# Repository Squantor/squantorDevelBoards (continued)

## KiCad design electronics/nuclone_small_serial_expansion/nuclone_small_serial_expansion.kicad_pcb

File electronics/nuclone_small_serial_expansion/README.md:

# Nuclone expansion board with FTDI/UART connection
Nuclone expansion board with UART connection, prototyping area and some connections
# HSI (Hardware Software Interface)
No real HSI, UART RX/TX brought outside
## TODO's
Still some things need to be done:
* schematic entry 
* PCB layout
* Review with one night in between
* Produce at [OSHPARK](https://oshpark.com/)
* Assemble
* Test & characterise
* update Readme.md with pictures and BOM
## BOM
* bunch of JST-PH connectors

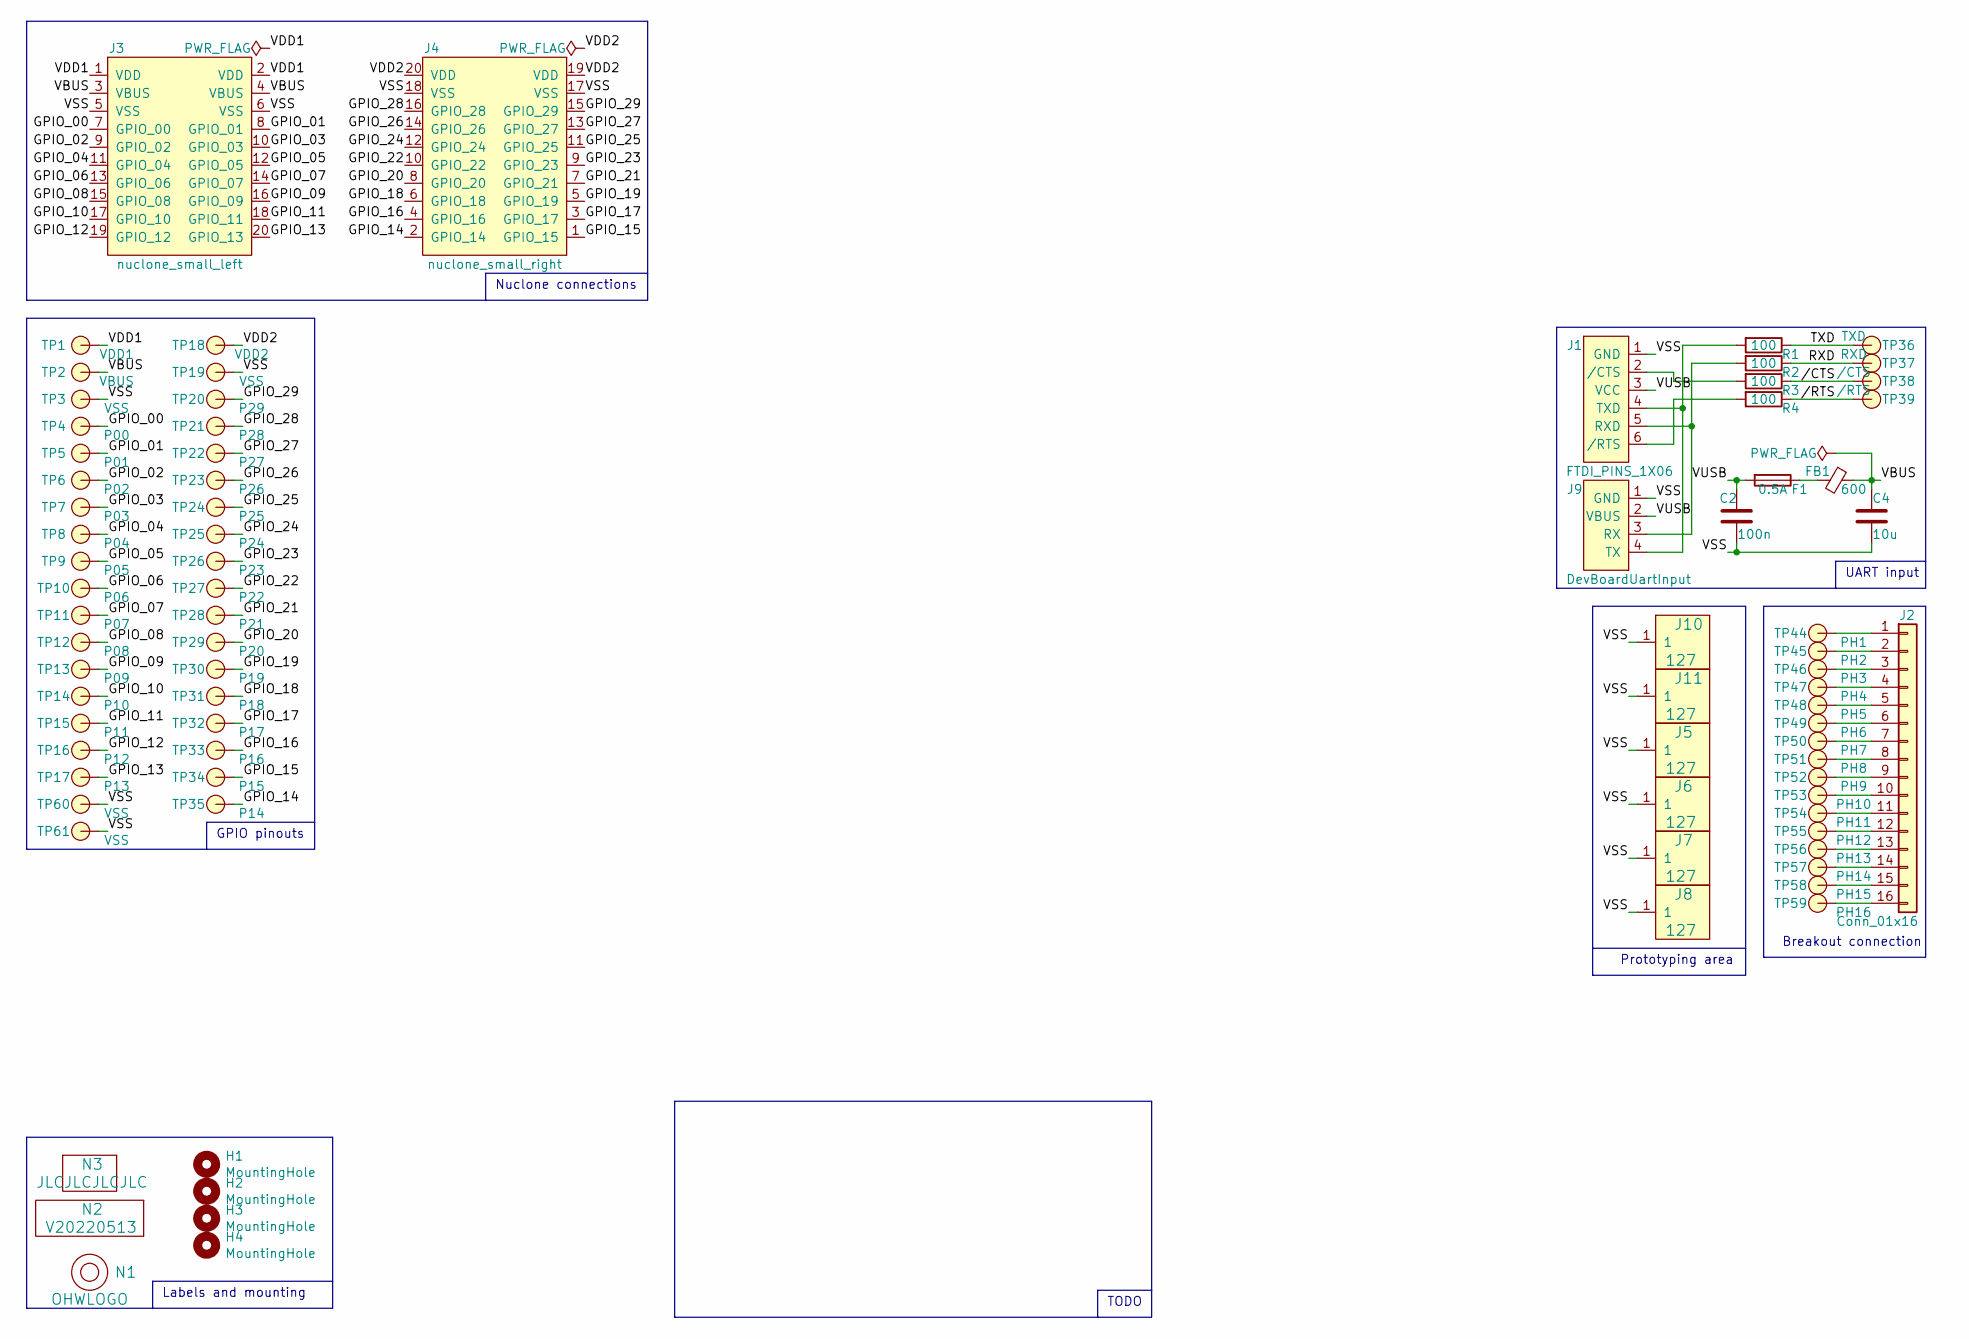
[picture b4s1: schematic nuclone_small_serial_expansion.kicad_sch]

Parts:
C2: 100n; C_0603
C4: 10u; C_0603
F1: 0.5A; F_0603_hand
FB1: 600; L_0603
H1, H2, H3, H4: MountingHole; MountingHole_3.2mm_M3_Pad_Via
J1: FTDI_PINS_1X06; PinHeader_1x06_P2.54mm_Horizontal
J2: Conn_01x16; JST_PH_S16B-PH-K_1x16_P2.00mm_Horizontal
J3: nuclone_small_left; nuclone_small_left_stacked
J4: nuclone_small_right; nuclone_small_right_stacked
J5, J6, J7, J8, J10, J11: 127; proto-SMD-0127-08X08-P010X020+pad
J9: DevBoardUartInput; JST_PH_S4B-PH-K_1x04_P2.00mm_Horizontal
N1: OHWLOGO; OSHW-Symbol_6.7x6mm_SilkScreen
N2: V20220513; Label_Generic
N3: JLCJLCJLCJLC; Label_Generic
R1, R2, R3, R4: 100; R_0603_hand
TP1: VDD1; TestPoint_hole_H05R10
TP2: VBUS; TestPoint_hole_H05R10
TP3, TP19, TP60, TP61: VSS; TestPoint_hole_H05R10
TP4: P00; TestPoint_hole_H05R10
TP5: P01; TestPoint_hole_H05R10
TP6: P02; TestPoint_hole_H05R10
TP7: P03; TestPoint_hole_H05R10
TP8: P04; TestPoint_hole_H05R10
TP9: P05; TestPoint_hole_H05R10
TP10: P06; TestPoint_hole_H05R10
TP11: P07; TestPoint_hole_H05R10
TP12: P08; TestPoint_hole_H05R10
TP13: P09; TestPoint_hole_H05R10
TP14: P10; TestPoint_hole_H05R10
TP15: P11; TestPoint_hole_H05R10
TP16: P12; TestPoint_hole_H05R10
TP17: P13; TestPoint_hole_H05R10
TP18: VDD2; TestPoint_hole_H05R10
TP20: P29; TestPoint_hole_H05R10
TP21: P28; TestPoint_hole_H05R10
TP22: P27; TestPoint_hole_H05R10
TP23: P26; TestPoint_hole_H05R10
TP24: P25; TestPoint_hole_H05R10
TP25: P24; TestPoint_hole_H05R10
TP26: P23; TestPoint_hole_H05R10
TP27: P22; TestPoint_hole_H05R10
TP28: P21; TestPoint_hole_H05R10
TP29: P20; TestPoint_hole_H05R10
TP30: P19; TestPoint_hole_H05R10
TP31: P18; TestPoint_hole_H05R10
TP32: P17; TestPoint_hole_H05R10
TP33: P16; TestPoint_hole_H05R10
TP34: P15; TestPoint_hole_H05R10
TP35: P14; TestPoint_hole_H05R10
TP36: TXD; TestPoint_hole_H05R10
TP37: RXD; TestPoint_hole_H05R10
TP38: /CTS; TestPoint_hole_H05R10
TP39: /RTS; TestPoint_hole_H05R10
TP44: PH1; TestPoint_hole_H05R10
TP45: PH2; TestPoint_hole_H05R10
TP46: PH3; TestPoint_hole_H05R10
TP47: PH4; TestPoint_hole_H05R10
TP48: PH5; TestPoint_hole_H05R10
TP49: PH6; TestPoint_hole_H05R10
TP50: PH7; TestPoint_hole_H05R10
TP51: PH8; TestPoint_hole_H05R10
TP52: PH9; TestPoint_hole_H05R10
TP53: PH10; TestPoint_hole_H05R10
TP54: PH11; TestPoint_hole_H05R10
TP55: PH12; TestPoint_hole_H05R10
TP56: PH13; TestPoint_hole_H05R10
TP57: PH14; TestPoint_hole_H05R10
TP58: PH15; TestPoint_hole_H05R10
TP59: PH16; TestPoint_hole_H05R10

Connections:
/GPIO_00: J3.7 (GPIO_00), TP4.1
/GPIO_01: J3.8 (GPIO_01), TP5.1
/GPIO_02: J3.9 (GPIO_02), TP6.1
/GPIO_03: J3.10 (GPIO_03), TP7.1
/GPIO_04: J3.11 (GPIO_04), TP8.1
/GPIO_05: J3.12 (GPIO_05), TP9.1
/GPIO_06: J3.13 (GPIO_06), TP10.1
/GPIO_07: J3.14 (GPIO_07), TP11.1
/GPIO_08: J3.15 (GPIO_08), TP12.1
/GPIO_09: J3.16 (GPIO_09), TP13.1
/GPIO_10: J3.17 (GPIO_10), TP14.1
/GPIO_11: J3.18 (GPIO_11), TP15.1
/GPIO_12: J3.19 (GPIO_12), TP16.1
/GPIO_13: J3.20 (GPIO_13), TP17.1
/GPIO_14: J4.2 (GPIO_14), TP35.1
/GPIO_15: J4.1 (GPIO_15), TP34.1
/GPIO_16: J4.4 (GPIO_16), TP33.1
/GPIO_17: J4.3 (GPIO_17), TP32.1
/GPIO_18: J4.6 (GPIO_18), TP31.1
/GPIO_19: J4.5 (GPIO_19), TP30.1
/GPIO_20: J4.8 (GPIO_20), TP29.1
/GPIO_21: J4.7 (GPIO_21), TP28.1
/GPIO_22: J4.10 (GPIO_22), TP27.1
/GPIO_23: J4.9 (GPIO_23), TP26.1
/GPIO_24: J4.12 (GPIO_24), TP25.1
/GPIO_25: J4.11 (GPIO_25), TP24.1
/GPIO_26: J4.14 (GPIO_26), TP23.1
/GPIO_27: J4.13 (GPIO_27), TP22.1
/GPIO_28: J4.16 (GPIO_28), TP21.1
/GPIO_29: J4.15 (GPIO_29), TP20.1
/RXD: R2.1, TP37.1
/TXD: R1.1, TP36.1
/VBUS: C4.1, FB1.1, J3.3 (VBUS), J3.4 (VBUS), TP2.1
/VDD1: J3.1 (VDD), J3.2 (VDD), TP1.1
/VDD2: J4.19 (VDD), J4.20 (VDD), TP18.1
/VSS: C2.2, C4.2, J1.1 (GND), J3.5 (VSS), J3.6 (VSS), J4.17 (VSS), J4.18 (VSS), J5.1, J6.1, J7.1, J8.1, J9.1 (GND), J10.1, J11.1, TP3.1, TP19.1, TP60.1, TP61.1
/VUSB: C2.1, F1.2, J1.3 (VCC), J9.2 (VBUS)
//CTS: R3.1, TP38.1
//RTS: R4.1, TP39.1
unnamed: F1.1, FB1.2
unnamed: J1.2 (/CTS), R3.2
unnamed: J1.4 (TXD), J9.4 (TX), R1.2
unnamed: J1.5 (RXD), J9.3 (RX), R2.2
unnamed: J1.6 (/RTS), R4.2
unnamed: J2.1, TP44.1
unnamed: J2.2, TP45.1
unnamed: J2.3, TP46.1
unnamed: J2.4, TP47.1
unnamed: J2.5, TP48.1
unnamed: J2.6, TP49.1
unnamed: J2.7, TP50.1
unnamed: J2.8, TP51.1
unnamed: J2.9, TP52.1
unnamed: J2.10, TP53.1
unnamed: J2.11, TP54.1
unnamed: J2.12, TP55.1
unnamed: J2.13, TP56.1
unnamed: J2.14, TP57.1
unnamed: J2.15, TP58.1
unnamed: J2.16, TP59.1

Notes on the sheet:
Prototyping area
Labels and mounting
Breakout connection
TODO
GPIO pinouts
UART input
Nuclone connections

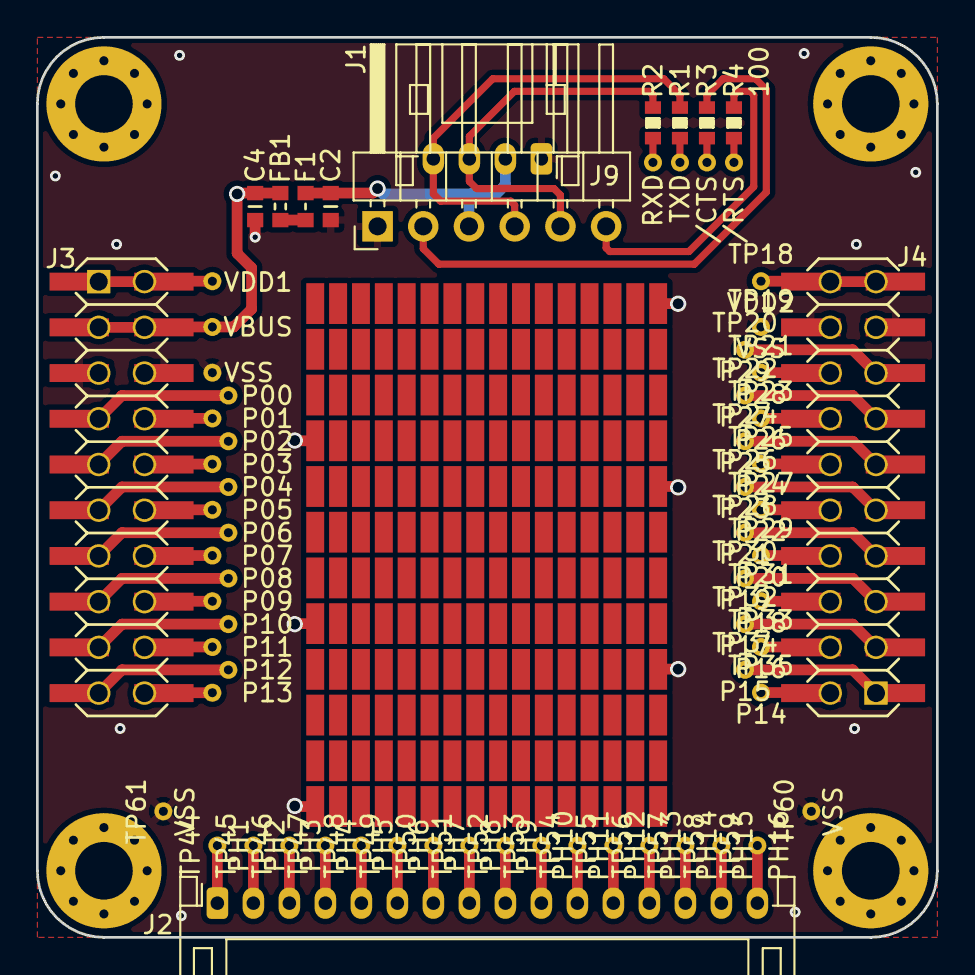
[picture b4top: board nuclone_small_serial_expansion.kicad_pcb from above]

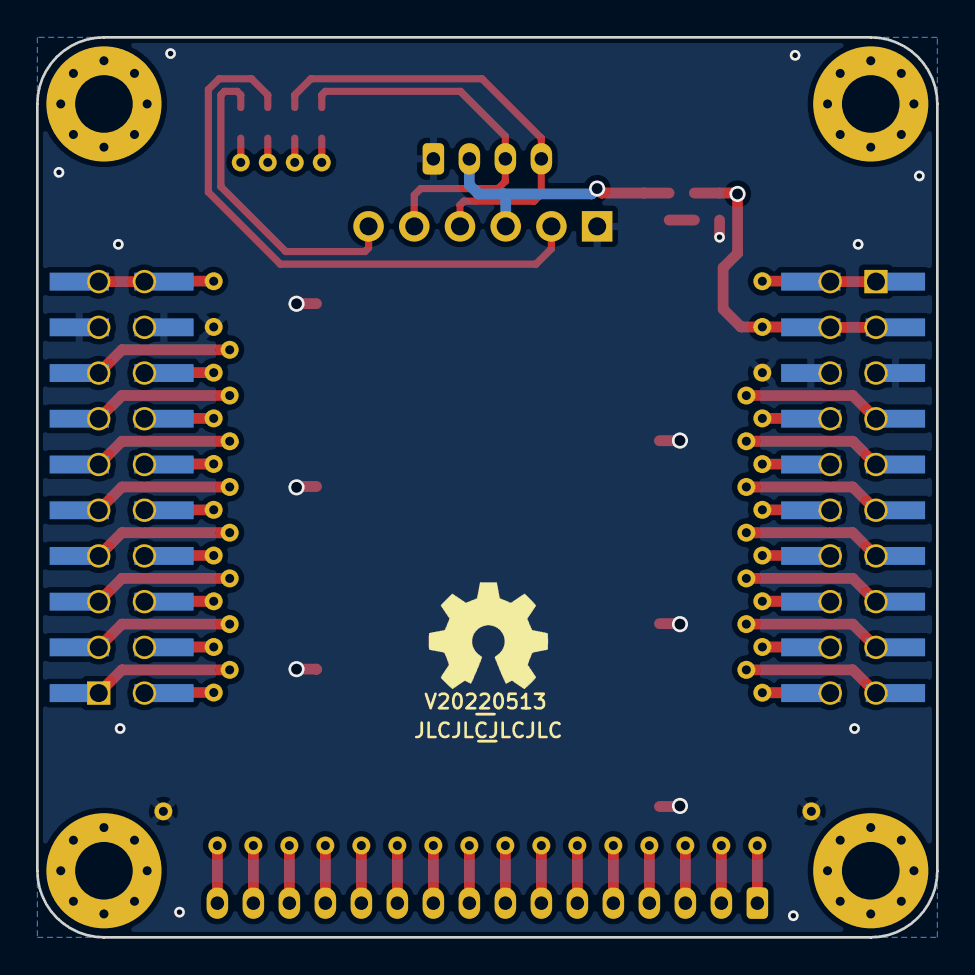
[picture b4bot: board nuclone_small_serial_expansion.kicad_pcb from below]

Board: 2 copper layers, 50.0 x 50.0 mm, 83 parts (3 on the bottom side), 60 nets.
